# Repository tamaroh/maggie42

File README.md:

# maggie42

maggie42は  
カスタムキーボードです。
- 左右対称カラムスタッガード
- 自然にハの字に手が配置される
- 傾けないレイアウトでキーの隙間がない
- 小指から弧を描く配列
- Pro Microに対応
- All 1Uレイアウト

## 必要なもの
|品名|数量|備考|入手先|
|----|----|----|----|
|PCB|1枚|
|キープレート|2枚|裏表はありません|
|ボトムプレート|1枚|
|M2ネジ 5mm|20本||遊舎工房など
|M2スペーサー 7mm|10個||遊舎工房など
|Pro Micro|1個|すべての互換品については動作を保障しません*|遊舎工房など
|ピンヘッダー|12Pin x 2個|コンスルー対応|遊舎工房など
|タクトスイッチ|1個||遊舎工房など
|USBケーブル|1本||遊舎工房など
|ダイオード|42個|SMD/スルーホール対応|遊舎工房など
|キーソケット|42個|Cherry MX互換のみ対応|遊舎工房など
|キースイッチ|42個|Cherry MX互換のみ対応|遊舎工房など
|キーキャップ|セット|すべて1Uです|遊舎工房など

* 厚さの異なるPro Micro互換品（USB-Cコネクタのタイプ）などの場合、コンスルーでは動作を保障できません。
  確実に接続できるピンヘッダ接続をおすすめします。

## 必要な工具
- はんだごて
- コテ台、コテ先クリーナー
- はんだ
- 精密ドライバー
- ピンセット

## 必要なソフトウェア
- [qmk toolbox](https://github.com/qmk/qmk_toolbox/releases)

## 制作手順
手順は人により異なりますが
1. Pro Microにファームウェアを書き込みます。
  - QMK Toolboxを起動し、書き込むファームウェア（下記参照）を選択しておきます。
  - USBをPCに接続して、リセットスイッチを押します。
  - 書き込み可能状態になったら、Flashボタンをクリックして書き込みます。
  - 書き込みが完了したらUSBケーブルを接続し直します。
2. ダイオードを半田付けします。SMDの場合縦線が入っている方の端子、スルーホールの場合黒い線がある方の端子を、基板上の縦線がある側に接続してください。

3. Pro Microを用意します。
   コンスルーを使用する場合は基板に差し込んでから、適切にPro Microに半田付けしてください。
   
   ピンヘッダを使用する場合は向きや表裏を間違えないようにします。
   ※USB-Cタイプなど、USBコネクタ部の場合はピンヘッダの高さが合わなかったり、コンスルーが抜けやすくなる可能性があります。
   
4. ソケットを半田付けします。シルク印刷に合わせて、スイッチの穴を塞がないようにします。
   
5. リセットスイッチを半田付けします。
   
6. キースイッチを4個程度、先にキープレートに差し込みます。
7. 基板と接続します。スイッチのピンが曲がらないように上からまっすぐ抑えます。
8. 残りのスイッチを差し込みます。ソケットとスイッチを指で挟み込むようにして、ソケットに確実に差し込みます。
9. 
10. PCBとキースイッチを接続します。
11. キーキャップを乗せます。
12. できあがり

## ファームウェアについて
ファームウェアは以下にあります。
https://github.com/tamaroh/maggie42/tree/main/firmware
|種別|ファイル名|備考
|----|----|----|
|QMK|maggie42_default.hex||
|VIA|maggie42_via.json||
|VIAL|maggie42_vial.hex|

ソースコードはこちら：https://github.com/tamaroh/qmk_firmware/tree/tamaroh/keyboards/tamaroh/maggie42
## 注意事項
- 自作キーボードについての知識がある方を対象としています。
- 非販売品につき、サポートは対象外としております。

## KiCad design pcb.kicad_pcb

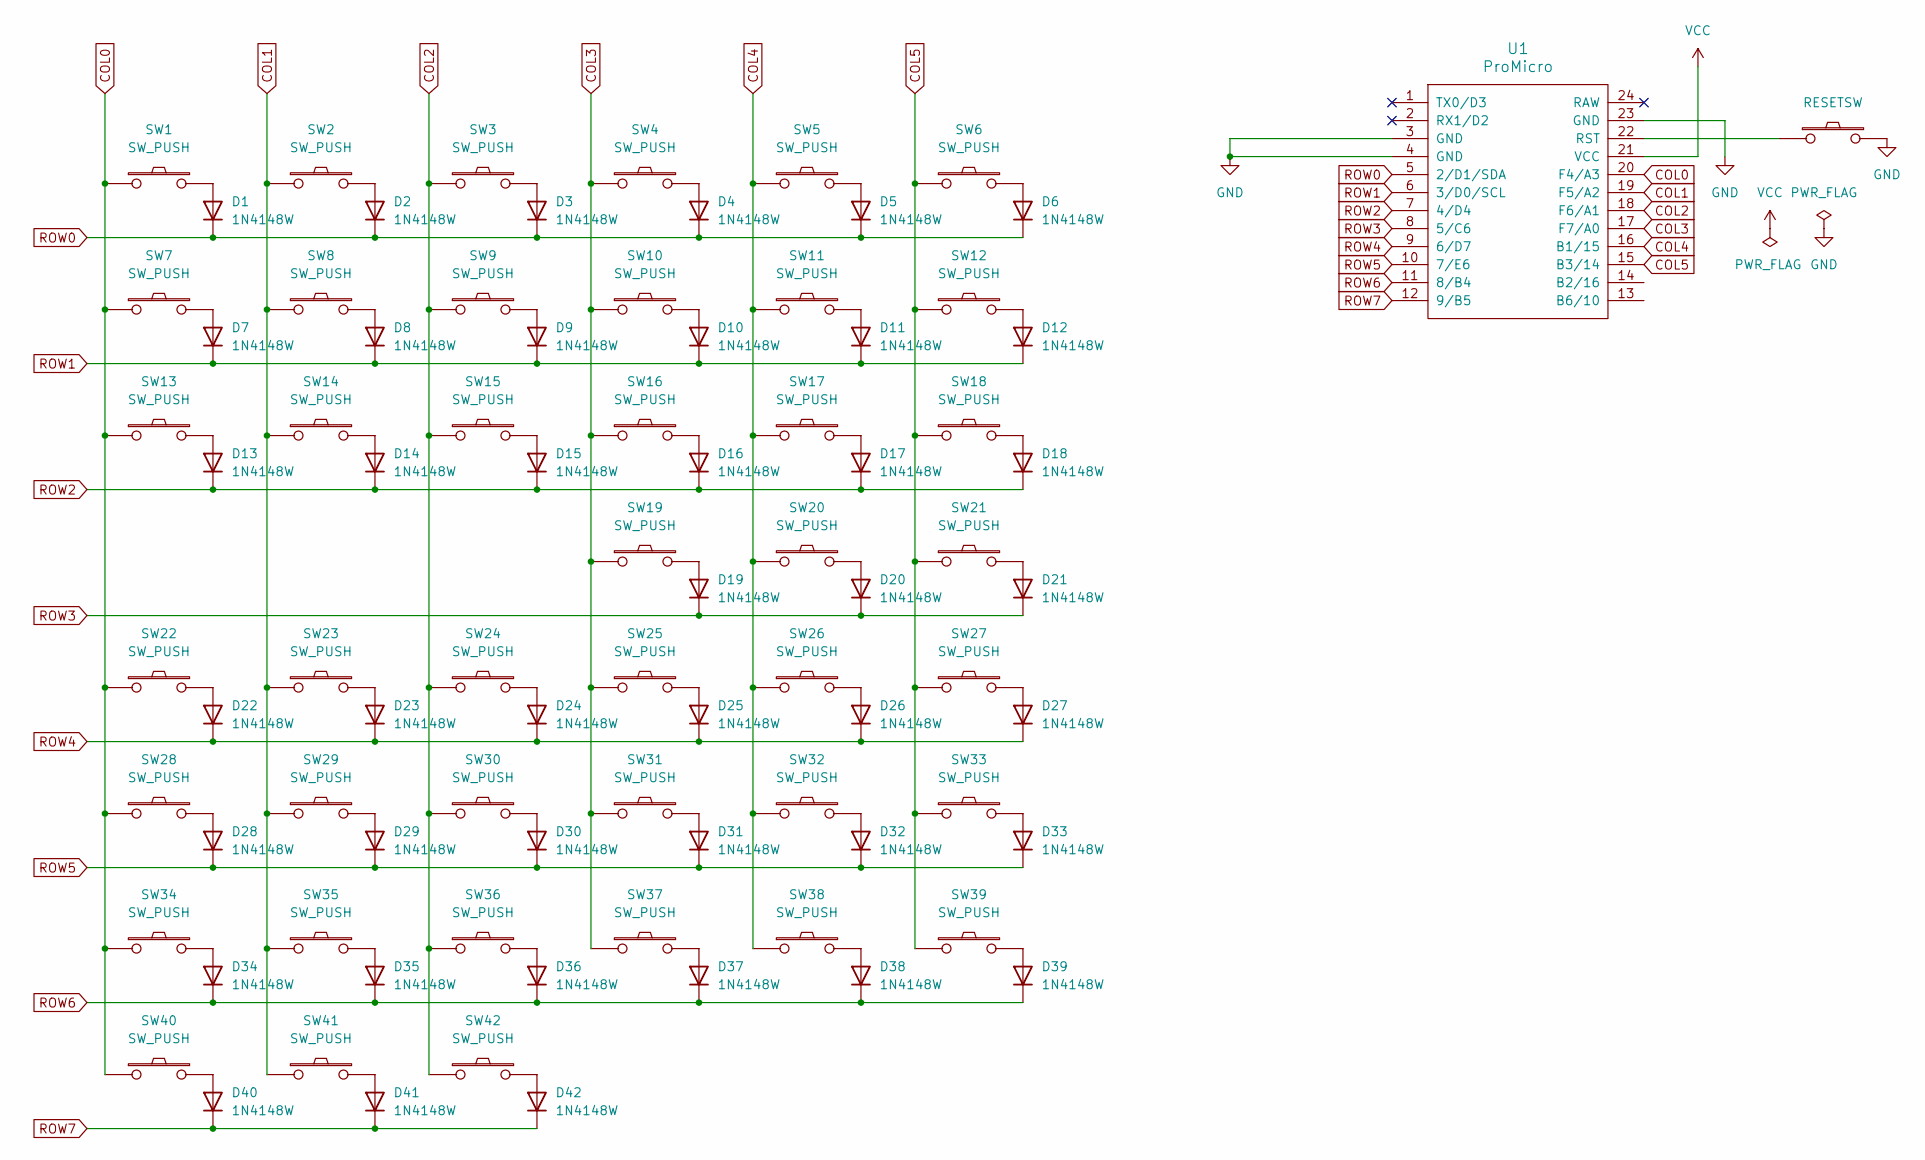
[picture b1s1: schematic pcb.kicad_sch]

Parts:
D1, D2, D3, D4, D5, D6, D7, D8, D9, D10, D11, D12, D13, D14, D15, D16, D17, D18, D19, D20, D21, D22, D23, D24, D25, D26, D27, D28, D29, D30, D31, D32, D33, D34, D35, D36, D37, D38, D39, D40, D41, D42: 1N4148W; D3_TH_SMD_v2
RSSW0: RESETSW; ResetSW_1side
SW1, SW2, SW3, SW4, SW5, SW6, SW7, SW8, SW9, SW10, SW11, SW12, SW13, SW14, SW15, SW16, SW17, SW18, SW19, SW20, SW21, SW22, SW23, SW24, SW25, SW26, SW27, SW28, SW29, SW30, SW31, SW32, SW33, SW34, SW35, SW36, SW37, SW38, SW39, SW40, SW41, SW42: SW_PUSH; CherryMX_Hotswap
U1: ProMicro; ProMicro_v3.5

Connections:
COL0: SW1.1, SW7.1, SW13.1, SW22.1, SW28.1, SW34.1, SW40.1, U1.20 (F4/A3)
COL1: SW2.1, SW8.1, SW14.1, SW23.1, SW29.1, SW35.1, SW41.1, U1.19 (F5/A2)
COL2: SW3.1, SW9.1, SW15.1, SW24.1, SW30.1, SW36.1, SW42.1, U1.18 (F6/A1)
COL3: SW4.1, SW10.1, SW16.1, SW19.1, SW25.1, SW31.1, SW37.1, U1.17 (F7/A0)
COL4: SW5.1, SW11.1, SW17.1, SW20.1, SW26.1, SW32.1, SW38.1, U1.16 (B1/15)
COL5: SW6.1, SW12.1, SW18.1, SW21.1, SW27.1, SW33.1, SW39.1, U1.15 (B3/14)
GND: RSSW0.2, U1.3 (GND), U1.4 (GND), U1.23 (GND)
unnamed: D1.2 (A), SW1.2
unnamed: D2.2 (A), SW2.2
unnamed: D3.2 (A), SW3.2
unnamed: D4.2 (A), SW4.2
unnamed: D5.2 (A), SW5.2
unnamed: D6.2 (A), SW6.2
unnamed: D7.2 (A), SW7.2
unnamed: D8.2 (A), SW8.2
unnamed: D9.2 (A), SW9.2
unnamed: D10.2 (A), SW10.2
unnamed: D11.2 (A), SW11.2
unnamed: D12.2 (A), SW12.2
unnamed: D13.2 (A), SW13.2
unnamed: D14.2 (A), SW14.2
unnamed: D15.2 (A), SW15.2
unnamed: D16.2 (A), SW16.2
unnamed: D17.2 (A), SW17.2
unnamed: D18.2 (A), SW18.2
unnamed: D19.2 (A), SW19.2
unnamed: D20.2 (A), SW20.2
unnamed: D21.2 (A), SW21.2
unnamed: D22.2 (A), SW22.2
unnamed: D23.2 (A), SW23.2
unnamed: D24.2 (A), SW24.2
unnamed: D25.2 (A), SW25.2
unnamed: D26.2 (A), SW26.2
unnamed: D27.2 (A), SW27.2
unnamed: D28.2 (A), SW28.2
unnamed: D29.2 (A), SW29.2
unnamed: D30.2 (A), SW30.2
unnamed: D31.2 (A), SW31.2
unnamed: D32.2 (A), SW32.2
unnamed: D33.2 (A), SW33.2
unnamed: D34.2 (A), SW34.2
unnamed: D35.2 (A), SW35.2
unnamed: D36.2 (A), SW36.2
unnamed: D37.2 (A), SW37.2
unnamed: D38.2 (A), SW38.2
unnamed: D39.2 (A), SW39.2
unnamed: D40.2 (A), SW40.2
unnamed: D41.2 (A), SW41.2
unnamed: D42.2 (A), SW42.2
unnamed: RSSW0.1, U1.22 (RST)
ROW0: D1.1 (K), D2.1 (K), D3.1 (K), D4.1 (K), D5.1 (K), D6.1 (K), U1.5 (2/D1/SDA)
ROW1: D7.1 (K), D8.1 (K), D9.1 (K), D10.1 (K), D11.1 (K), D12.1 (K), U1.6 (3/D0/SCL)
ROW2: D13.1 (K), D14.1 (K), D15.1 (K), D16.1 (K), D17.1 (K), D18.1 (K), U1.7 (4/D4)
ROW3: D19.1 (K), D20.1 (K), D21.1 (K), U1.8 (5/C6)
ROW4: D22.1 (K), D23.1 (K), D24.1 (K), D25.1 (K), D26.1 (K), D27.1 (K), U1.9 (6/D7)
ROW5: D28.1 (K), D29.1 (K), D30.1 (K), D31.1 (K), D32.1 (K), D33.1 (K), U1.10 (7/E6)
ROW6: D34.1 (K), D35.1 (K), D36.1 (K), D37.1 (K), D38.1 (K), D39.1 (K), U1.11 (8/B4)
ROW7: D40.1 (K), D41.1 (K), D42.1 (K), U1.12 (9/B5)
VCC: U1.21 (VCC)

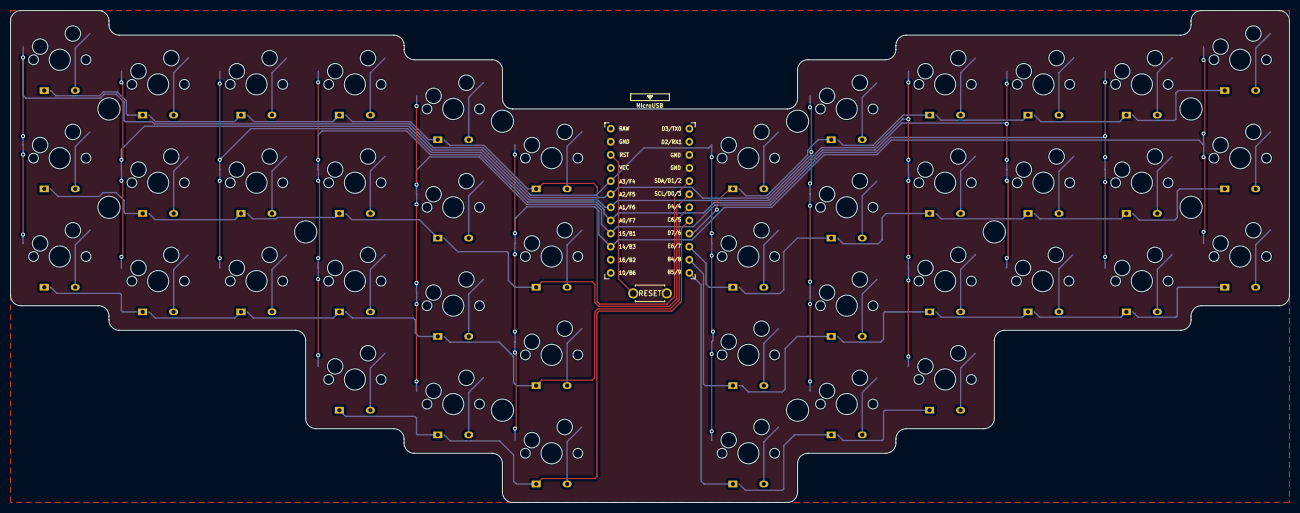
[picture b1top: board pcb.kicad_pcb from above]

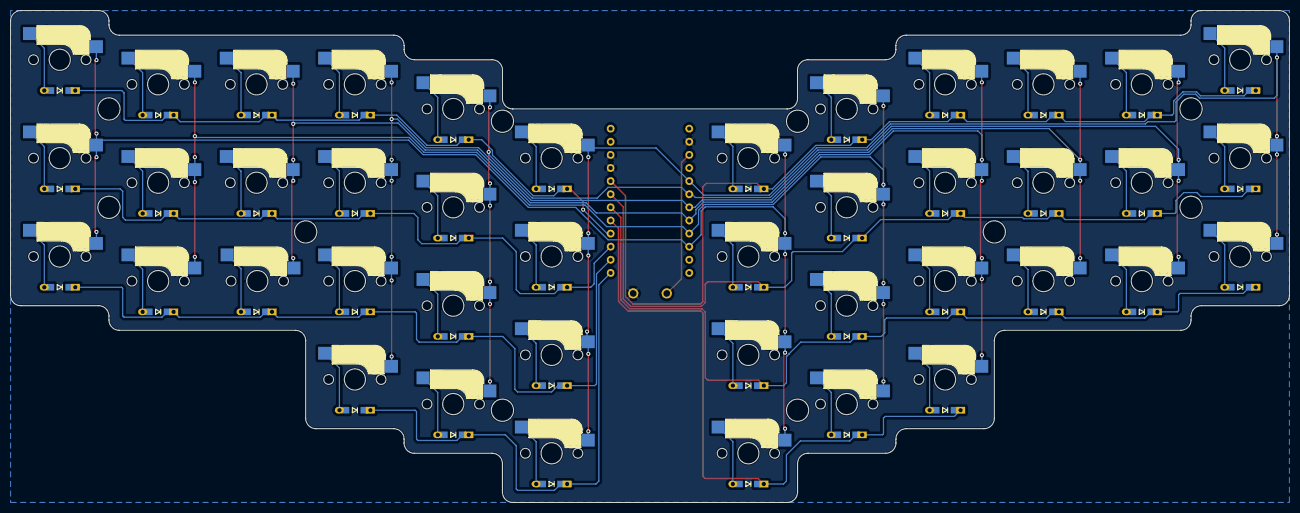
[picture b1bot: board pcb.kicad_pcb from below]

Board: 2 copper layers, 247.7 x 95.2 mm, 96 parts (42 on the bottom side), 58 nets.

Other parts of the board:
Ref**: Val**; spacer_m2
Ref**#2, Ref**#3, Ref**#4, Ref**#5, Ref**#6, Ref**#7, Ref**#8, Ref**#9, Ref**#10: Val**; spacer_m2

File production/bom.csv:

Designator,Footprint,Quantity,Value,LCSC Part #
"D1, D10, D11, D12, D13, D14, D15, D16, D17, D18, D19, D2, D20, D21, D22, D23, D24, D25, D26, D27, D28, D29, D3, D30, D31, D32, D33, D34, D35, D36, D37, D38, D39, D4, D40, D41, D42, D5, D6, D7, D8, D9",D3_TH_SMD_v2,42,1N4148W,
RSSW0,ResetSW_1side,1,RESETSW,
"SW1, SW10, SW11, SW12, SW13, SW14, SW15, SW16, SW17, SW18, SW19, SW2, SW20, SW21, SW22, SW23, SW24, SW25, SW26, SW27, SW28, SW29, SW3, SW30, SW31, SW32, SW33, SW34, SW35, SW36, SW37, SW38, SW39, SW4, SW40, SW41, SW42, SW5, SW6, SW7, SW8, SW9",CherryMX_Hotswap,42,SW_PUSH,
U1,ProMicro_v3,1,ProMicro,

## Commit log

2023-06-04 add submodule
2023-06-05 create circuit
2023-06-05 rename repo and folder
2023-06-05 fixed switch numbering
2023-06-05 assigned footprint
2023-06-06 fixed lines
2023-06-06 refactored wiring
2023-06-07 set hole
2023-06-09 create garbar file
2023-06-10 changed top-plate half-size
2023-06-13 added bottom plate
2023-06-13 added order svg file for yushakobo
2023-06-13 added 300x110
2023-06-18 added firmware files
2023-06-18 added vial firmware
2023-10-31 add gitignore
2023-10-31 added via json
2023-10-31 added readme, draft
2023-10-31 added images, wip
2023-12-27 added test svg files
